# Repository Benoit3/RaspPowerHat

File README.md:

# RaspPowerHat
A raspberry hat designed to manage raspberry powering from a car battery.<br>
The purpose of the hat is to switch on the RaspBerry when car accessory power is switched on (easy ;-) ) and to switch it off properly (after linux shutdown ) when the car accessory power is switched off (more difficult).

If the PI is not halted 10 minutes after accessory power switch off, the power supply of the PI is cut to avoid to dry the battery.

To achieve this objective, the raspberry itself is powered by a permanent +12V power line through a 5V step down converter. A connection to ACC power supply (switched ignition) allow to switch on and later off the raspberry.<br>

The Hat PCB is designed to fit well on a Raspberry PI Z but can also be used on Raspberry 2 or 3.<br/>

Black wire is for ground, red for permanent 12 to 24 V, yellow is for accessories ON or ignition On information

One limitation is the output current of the 5V converter which is 2A. This is the biggest converter I found which can be soldered on the back of the PCB.

The Hat is build using an ATTINY 45.

You can get information about [Hardware and PCB](PCB/README.md), [Firmware](Firmware/README.md) and [PI test software](Software/README.md)

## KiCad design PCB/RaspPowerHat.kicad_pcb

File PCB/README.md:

This folder contains definition of the electronic part of the Hat. 

Schematic and PCBs habe made starting with [template from mikelawrence](https://github.com/mikelawrence/RPi_Zero_pHat_Template). 
Files can be edited with [Kicad PCB](http://www.kicad-pcb.org/) , a Cross Platform and Open Source Electronics Design Automation Suite .

Some explanation :
- U2 BTS452T is a Smart Power Switch to power the PI through the Traco regulator TSR 2-2450. C3 is not mandatory but recommended by the Traco application note if input voltage of 24V is used. 
- D1 and D5 are to power the 78L33 regulator and then the arduino ATTINY 45 from Vacc or from the U2 power switch.
- In case of usage with a 24V car battery, in charge voltage can grow up to 28 V (normal operation) or even 32 V (overvoltage situation). D2, D3, D4 are there to protect the 78L33 input (maximun rating 30V) in this case.
- R1 are R2 are a divider to provide Vacc voltage information to the ATTINY 45 through  analog input AN3.
- R4, R5 are pull-up for communication I2C bus between the ATTINY 45 and the PI
- JP1 : pin 1 and 2 need to be shorten as the SHUTDOWN request is now done through the I2C bus and not through a dedicated digital input
- J3, J4, R3, D6 are not necessary for a generci usage and were dedicated to data saving of GPS chipset
- R11, R12, R13, R14, U6, U7 are there for additionnal isolated input. But I've never sold neither tested them. Forget them.

References of used components can be browsed by opening schematic file (RaspPowerHat.sch) with KiCad PCB.

File package to order PCB manufacturing can be found [here](PCB.zip)

Here is the result with hand soldering. It is possible to use stackable header to add another PI hat on top of it.
The Hat is larger than a standard PI Zero one to the 5 leds.
- Front side:

The switched regulator TSR 2-2450 normaly sold on the front side (as on the design) can also be sold on the back side to adjust height of the PCB stack.
- Back side :

You can now find the ATTINY 45 firmware [here](../Firmware)

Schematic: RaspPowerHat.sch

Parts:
C1: 100 nF; C_1812_4532Metric_Pad1.30x3.40mm_HandSolder
C2: 330 nF; C_1812_4532Metric_Pad1.30x3.40mm_HandSolder
C3: 22 uF; C_2225_5664Metric_Pad1.80x6.60mm_HandSolder
D1, D2, D3, D4, D5: S1B; D_SMA
D6: MMSZ4685T1G; D_SOD-123
D7: B; LED_D3.0mm
D8: R; LED_D3.0mm
D9: J; LED_D3.0mm
D10, D11: V; LED_D3.0mm
F1: 1206L010/60WR; Fuse_1206_3216Metric_Pad1.42x1.75mm_HandSolder
F2: 29L110/60; Fuse_2920_7451Metric_Pad2.10x5.45mm_HandSolder
J1: Conn_01x05; TerminalBlock_Phoenix_MPT-0,5-5-2.54_1x05_P2.54mm_Horizontal
J2: RPi_GPIO; Pin_Header_Straight_2x20
J3, J4: GPS Backup; Pin_D1.4mm_L8.5mm_W2.8mm_FlatFork
JP1: SolderJumper_3_Open; SolderJumper-3_P1.3mm_Open_RoundedPad1.0x1.5mm_NumberLabels
R1, R3: 100 k; R_1206_3216Metric_Pad1.42x1.75mm_HandSolder
R2, R4, R11, R12, R13, R14: 10 k; R_1206_3216Metric_Pad1.42x1.75mm_HandSolder
R5: 10k; R_1206_3216Metric_Pad1.42x1.75mm_HandSolder
R6, R7, R8, R9, R10: 330; R_1206_3216Metric_Pad1.42x1.75mm_HandSolder
U2: BTS452T; TO-252-5_TabPin6
U3: TSR_2-2450; Converter_DCDC_TRACO_TSR-2_THT
U4: L78L33_SO8; SOIC-8_3.9x4.9mm_P1.27mm
U5: ATtiny45-20PU; DIP-8_W7.62mm
U6, U7: SFH6206-1T; SMDIP-4_W9.53mm_Clearance8mm

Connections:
/-HALTED: J2.37 (GPIO26), U5.3 (XTAL2/PB4)
/GND: C1.2, C2.2, C3.2, D6.2, J1.1, J2.9 (GND), R2.2, R11.1, R13.1, U2.1 (GND), U3.2 (GND), U4.2, U4.3, U4.6, U4.7, U5.4 (GND), U6.3, U7.3
/POWER_ON: U2.2 (IN), U5.6 (PB1)
/SHUTDOWN_REQUEST: J2.36 (GPIO16), JP1.3
/VCC: F2.1, R3.1, U2.6 (Vbb)
/Vacc: D5.2, F1.1, R1.1, R12.2, R14.1
unnamed: C1.1, U4.1, U5.8 (VCC)
unnamed: C2.1, D2.1, U4.8
unnamed: C3.1, D1.2, U2.5 (OUT), U3.1 (Vin)
unnamed: D1.1, D4.2, D5.1
unnamed: D2.2, D3.1
unnamed: D3.2, D4.1
unnamed: D6.1, J3.1, J4.1, R3.2
unnamed: D7.2, R6.1
unnamed: D8.2, R7.1
unnamed: D9.2, R8.1
unnamed: D7.1, D8.1, D9.1, D10.1, D11.1, J2.6 (GND)
unnamed: D10.2, R9.1
unnamed: D11.2, R10.1
unnamed: F1.2, J1.3
unnamed: F2.2, J1.2
unnamed: J1.4, U6.1
unnamed: J1.5, U7.1
unnamed: J2.1 (3.3V), R4.1, R5.1
unnamed: J2.2 (5V), J2.4 (5V), U3.3 (Vout)
unnamed: J2.3 (GPIO02_SDA1_I2C), JP1.1, R5.2
unnamed: J2.5 (GPIO03_SCL1_I2C), R4.2, U5.7 (PB2)
unnamed: J2.11 (GPIO17), R7.2
unnamed: J2.12 (GPIO18), R6.2
unnamed: J2.13 (GPIO27), R8.2
unnamed: J2.16 (GPIO23), R9.2
unnamed: J2.17 (3.3V), R10.2
unnamed: J2.29 (GPIO05), U6.4
unnamed: J2.31 (GPIO06), U7.4
unnamed: JP1.2, U5.5 (AREF/PB0)
unnamed: R1.2, R2.1, U5.2 (XTAL1/PB3)
unnamed: R11.2, R12.1, U6.2
unnamed: R13.2, R14.2, U7.2

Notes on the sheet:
Thru-Hole PI Connector

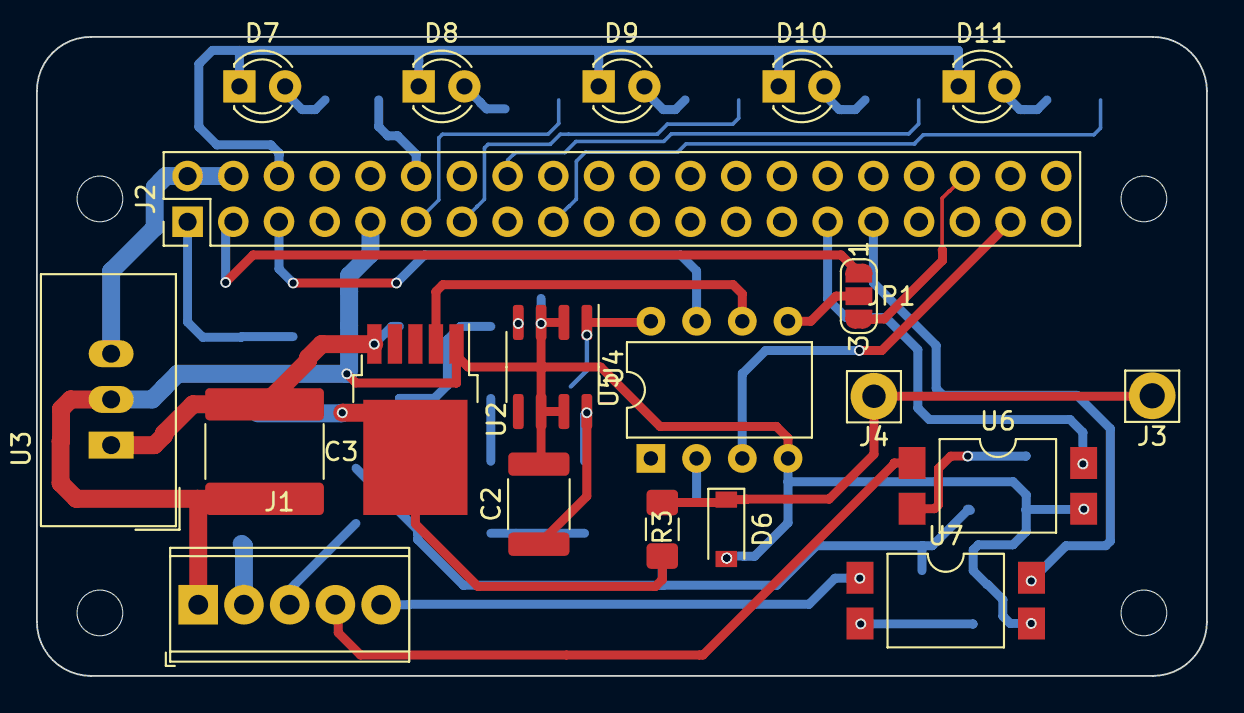
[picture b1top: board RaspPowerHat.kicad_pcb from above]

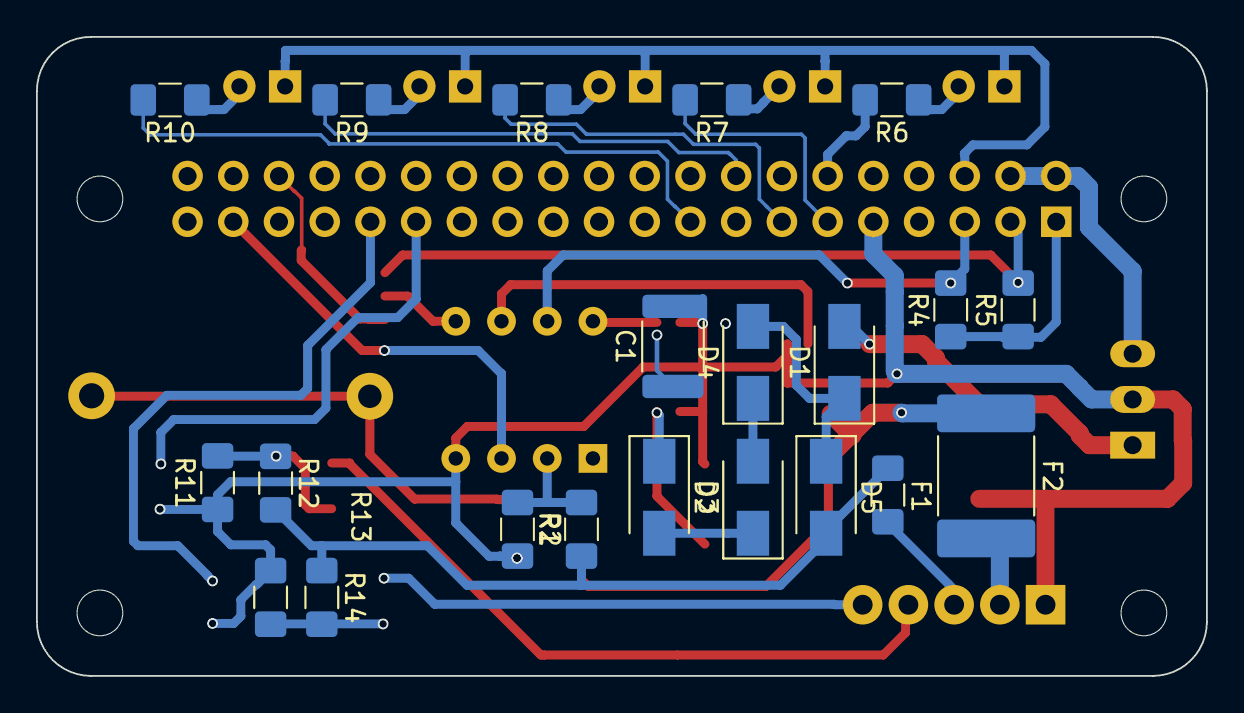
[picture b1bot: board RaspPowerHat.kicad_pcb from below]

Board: 2 copper layers, 65.0 x 35.5 mm, 41 parts (21 on the bottom side), 38 nets.

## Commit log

2019-10-21 update comment
2019-10-21 Add files via upload
    update hex with last compilation result
2019-10-30 Update README.md
    readme improvement
